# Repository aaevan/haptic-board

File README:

This is my first attempt at a driver board for 10 small vibration motors.

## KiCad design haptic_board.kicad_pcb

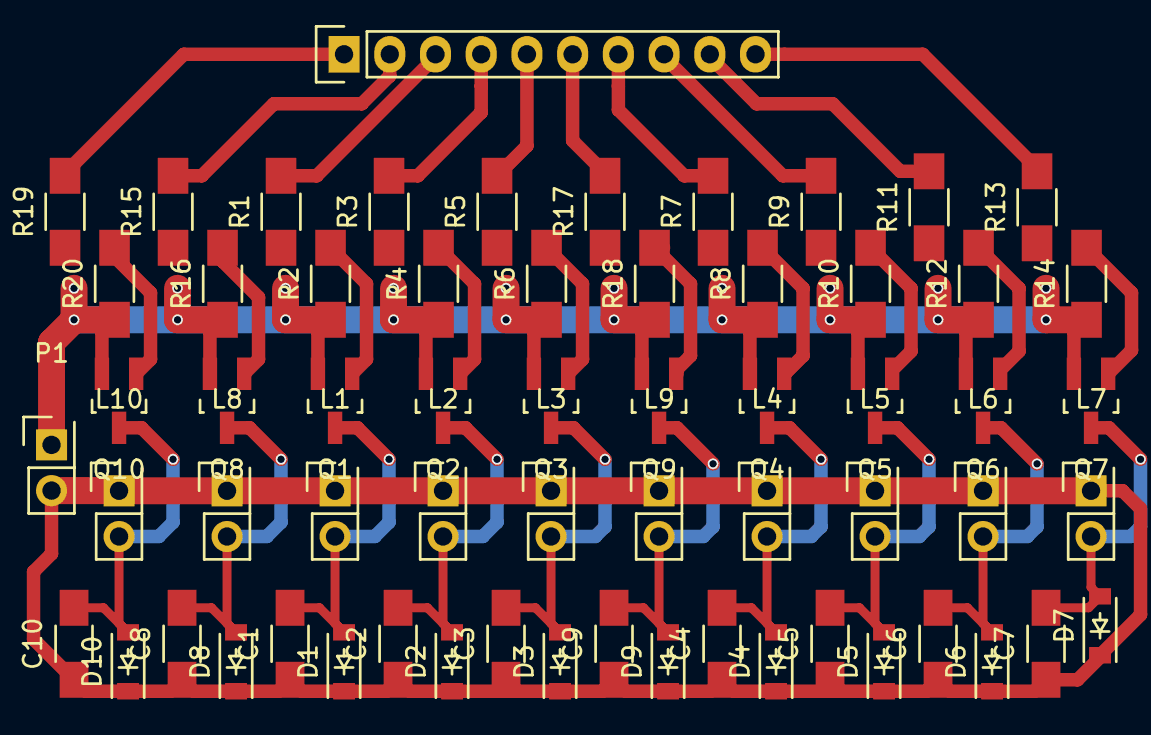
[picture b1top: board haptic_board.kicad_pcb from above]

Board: 2 copper layers, 62 parts (0 on the bottom side), 32 nets.

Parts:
C1, C2, C3, C4, C5, C6, C7, C8, C9, C10: C; C_1206_HandSoldering
D1, D2, D3, D4, D5, D6, D7, D8, D9, D10: D_Schottky; SOD-123
L1, L2, L3, L4, L5, L6, L7, L8, L9, L10: vibe_motor; Socket_Strip_Straight_2x01
P1: CONN_01X02; Socket_Strip_Straight_2x01
P2: CONN_01X10; Socket_Strip_Straight_1x10
Q1, Q2, Q3, Q4, Q5, Q6, Q7, Q8, Q9, Q10: 2N7002; SOT-23_Handsoldering
R1, R2, R3, R4, R5, R6, R7, R8, R9, R10, R11, R12, R13, R14, R15, R16, R17, R18, R19, R20: R; R_1206_HandSoldering

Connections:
/vibe_motor_driver_0/drive_pin: P2.1, R19.2
/vibe_motor_driver_1/drive_pin: P2.2, R15.2
/vibe_motor_driver_2/drive_pin: P2.3, R1.2
/vibe_motor_driver_3/drive_pin: P2.4, R3.2
/vibe_motor_driver_4/drive_pin: P2.5, R5.2
/vibe_motor_driver_5/drive_pin: P2.6, R17.2
/vibe_motor_driver_6/drive_pin: P2.7, R7.2
/vibe_motor_driver_7/drive_pin: P2.8, R9.2
/vibe_motor_driver_8/drive_pin: P2.9, R11.2
/vibe_motor_driver_9/drive_pin: P2.10, R13.2
GND: P1.1, Q1.2, Q2.2, Q3.2, Q4.2, Q5.2, Q6.2, Q7.2, Q8.2, Q9.2, Q10.2, R2.1, R4.1, R6.1, R8.1, R10.1, R12.1, R14.1, R16.1, R18.1, R20.1
unnamed: C1.2, D1.2, L1.2, Q1.3
unnamed: C2.2, D2.2, L2.2, Q2.3
unnamed: C3.2, D3.2, L3.2, Q3.3
unnamed: C4.2, D4.2, L4.2, Q4.3
unnamed: C5.2, D5.2, L5.2, Q5.3
unnamed: C6.2, D6.2, L6.2, Q6.3
unnamed: C7.2, D7.2, L7.2, Q7.3
unnamed: C8.2, D8.2, L8.2, Q8.3
unnamed: C9.2, D9.2, L9.2, Q9.3
unnamed: C10.2, D10.2, L10.2, Q10.3
unnamed: Q1.1, R1.1, R2.2
unnamed: Q2.1, R3.1, R4.2
unnamed: Q3.1, R5.1, R6.2
unnamed: Q4.1, R7.1, R8.2
unnamed: Q5.1, R9.1, R10.2
unnamed: Q6.1, R11.1, R12.2
unnamed: Q7.1, R13.1, R14.2
unnamed: Q8.1, R15.1, R16.2
unnamed: Q9.1, R17.1, R18.2
unnamed: Q10.1, R19.1, R20.2
VCC: C1.1, C2.1, C3.1, C4.1, C5.1, C6.1, C7.1, C8.1, C9.1, C10.1, D1.1, D2.1, D3.1, D4.1, D5.1, D6.1, D7.1, D8.1, D9.1, D10.1, L1.1, L2.1, L3.1, L4.1, L5.1, L6.1, L7.1, L8.1, L9.1, L10.1, P1.2

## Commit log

2016-07-31 First commit, first version of board.
2016-07-31 Added a readme.
2016-07-31 Added a render of the board.
